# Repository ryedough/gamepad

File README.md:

# Ryedough's Gamepad
a prototype of usb c gamepad using ch32v003 as mcu

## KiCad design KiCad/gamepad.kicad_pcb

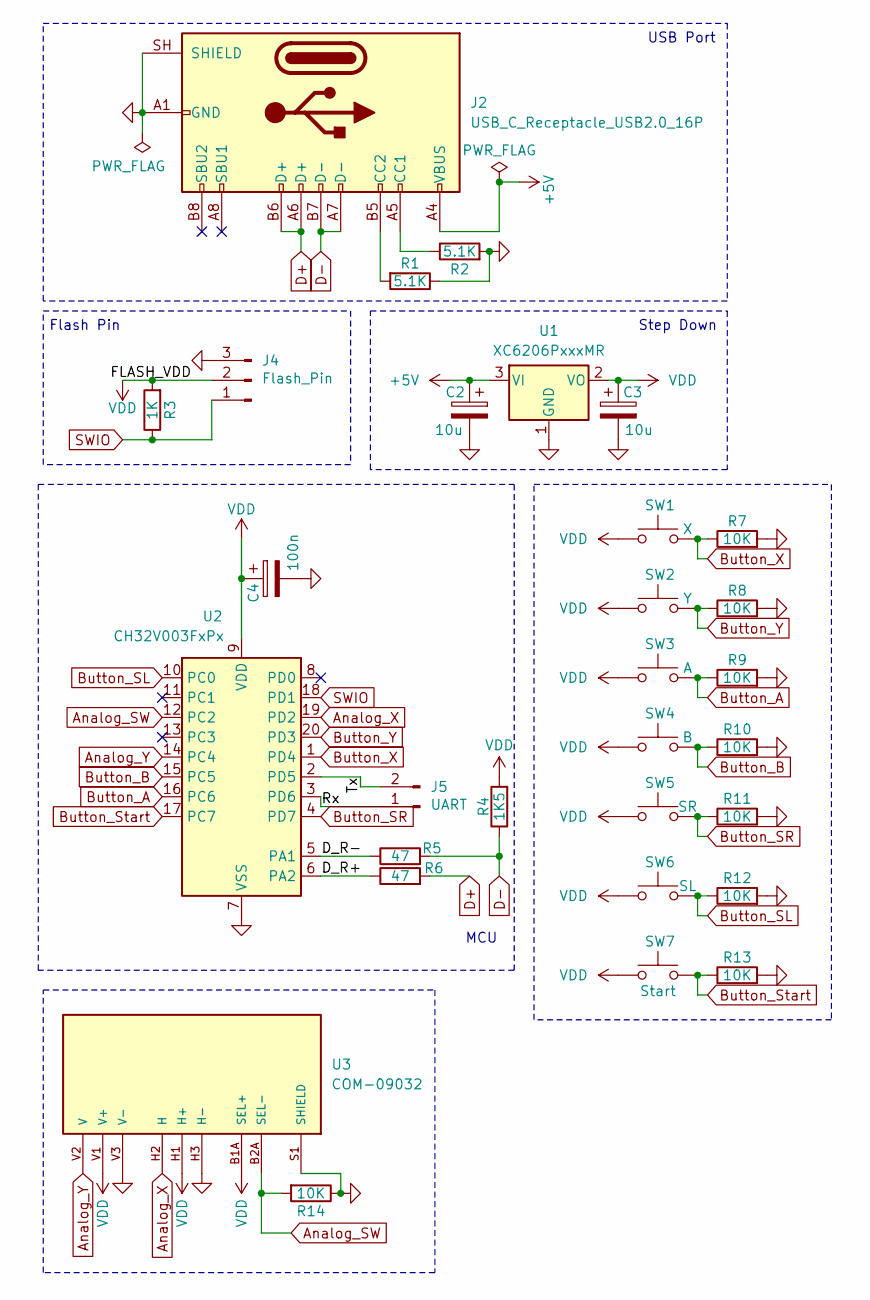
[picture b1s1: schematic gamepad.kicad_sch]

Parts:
C2, C3: 10u; CP_EIA-1608-10_AVX-L_HandSolder
C4: 100n; CP_EIA-1608-10_AVX-L_HandSolder
J2: USB_C_Receptacle_USB2.0_16P; USB_C_Receptacle_HRO_TYPE-C-31-M-12
J4: Flash_Pin; PinHeader_1x03_P2.54mm_Vertical
J5: UART; PinHeader_1x02_P2.54mm_Vertical
R1, R2: 5.1K; R_0805_2012Metric_Pad1.20x1.40mm_HandSolder
R3: 1K; R_0805_2012Metric_Pad1.20x1.40mm_HandSolder
R4: 1K5; R_0805_2012Metric_Pad1.20x1.40mm_HandSolder
R5, R6: 47; R_0805_2012Metric_Pad1.20x1.40mm_HandSolder
R7, R8, R9, R10, R11, R12, R13, R14: 10K; R_0805_2012Metric_Pad1.20x1.40mm_HandSolder
SW1: X; SW_PUSH_6mm
SW2: Y; SW_PUSH_6mm
SW3: A; SW_PUSH_6mm
SW4: B; SW_PUSH_6mm
SW5: SR; SolderWire-0.5sqmm_1x02_P4.6mm_D0.9mm_OD2.1mm
SW6: SL; SolderWire-0.5sqmm_1x02_P4.6mm_D0.9mm_OD2.1mm
SW7: Start; SW_PUSH_6mm
U1: XC6206PxxxMR; SOT-23-3
U2: CH32V003FxPx; TSSOP-20_4.4x6.5mm_P0.65mm
U3: COM-09032; XDCR_COM-09032; PARTREV N/A

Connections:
+5V: C2.1, J2.A4 (VBUS), J2.A9 (VBUS), J2.B4 (VBUS), J2.B9 (VBUS), U1.3 (VI)
/D_R+: R6.1, U2.6 (PA2)
/D_R-: R5.1, U2.5 (PA1)
/Rx: J5.1, U2.3 (PD6)
/Tx: J5.2, U2.2 (PD5)
Analog_SW: R14.2, U2.12 (PC2), U3.B2A (SEL-)
Analog_X: U2.19 (PD2), U3.H2 (H)
Analog_Y: U2.14 (PC4), U3.V2 (V)
Button_A: R9.1, SW3.2, U2.16 (PC6)
Button_B: R10.1, SW4.2, U2.15 (PC5)
Button_SL: R12.1, SW6.2, U2.10 (PC0)
Button_SR: R11.1, SW5.2, U2.4 (PD7)
Button_Start: R13.1, SW7.2, U2.17 (PC7)
Button_X: R7.1, SW1.2, U2.1 (PD4)
Button_Y: R8.1, SW2.2, U2.20 (PD3)
D+: J2.A6 (D+), J2.B6 (D+), R6.2
D-: J2.A7 (D-), J2.B7 (D-), R4.1, R5.2
GND: C2.2, C3.2, C4.2, J2.A1 (GND), J2.A12 (GND), J2.B1 (GND), J2.B12 (GND), J2.SH (SHIELD), J4.3, R1.1, R2.2, R7.2, R8.2, R9.2, R10.2, R11.2, R12.2, R13.2, R14.1, U1.1 (GND), U2.7 (VSS), U3.H3 (H-), U3.S1 (SHIELD), U3.S2 (SHIELD), U3.S3 (SHIELD), U3.S4 (SHIELD), U3.V3 (V-)
unnamed: J2.A5 (CC1), R2.1
unnamed: J2.B5 (CC2), R1.2
SWIO: J4.1, R3.1, U2.18 (PD1)
VDD: C3.1, C4.1, J4.2, R3.2, R4.2, SW1.1, SW2.1, SW3.1, SW4.1, SW5.1, SW6.1, SW7.1, U1.2 (VO), U2.9 (VDD), U3.B1A (SEL+), U3.H1 (H+), U3.V1 (V+)

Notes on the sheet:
USB Port
MCU
Flash Pin
Step Down

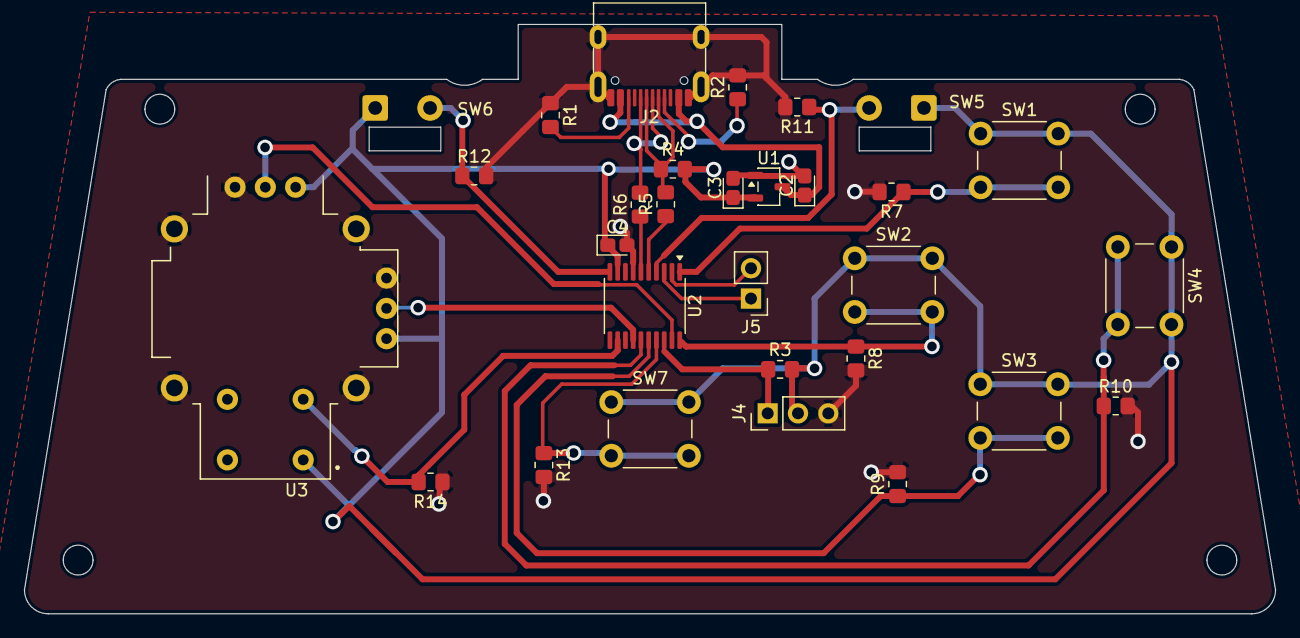
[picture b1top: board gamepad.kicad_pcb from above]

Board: 2 copper layers, 104.9 x 49.4 mm, 30 parts (0 on the bottom side), 22 nets.
